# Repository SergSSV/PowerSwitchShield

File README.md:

Power Switch Shield with S202S02
================================

Simple shield with [2N7002](http://www.nxp.com/documents/data_sheet/2N7002.pdf) MOSFET to drive the [S202S02](http://www.sharpsma.com/webfm_send/303) Solid State Relay.  
The board is panelized to have two sub-boards with one S202S02 and also
a sub-board with three S202S02.

Boards are available from [dirtypcbs.com.](http://dirtypcbs.com/view.php?share=17641&accesskey=2531b32f0bd15d34d1d7f6f8c30357b9)

The PCB contains spare places to solder pull-up / pull-down resistors.  
Pull-Up: R5, R8, R12, R14, R16  
Pull-Down: R6, R7, R13, R15, R17

Resistors (R1, R3, R18, R19, R20) are calculated to get 20mA current at 3.3V supply.  
By using larger values (180R) it may also be used as a 5V shield.

#WARNING
**The shield is designed to switch main power.** So you must care about proper isolation.  
Don't use metal nuts or bolds to fix the board - only use plastic ones!  
For **inductive loads** (e.g. motors) either **connect a [snubber](https://www.google.de/?gws_rd=ssl#q=snubber+circuit)** (surge absorption) circuit as close as possible to the AC clamps or use a *S202S11*.

For AC current > 1A you should consider to use a heat sink (see datasheet "Fig.2 RMS ON-state Current vs. 
Ambient Temperature")!

[Sharp Documentation: Use of Solid State Relays (SSRs)](http://www.datasheetarchive.com/dlmain/SFDatasheet-3/sf-00061711.pdf)

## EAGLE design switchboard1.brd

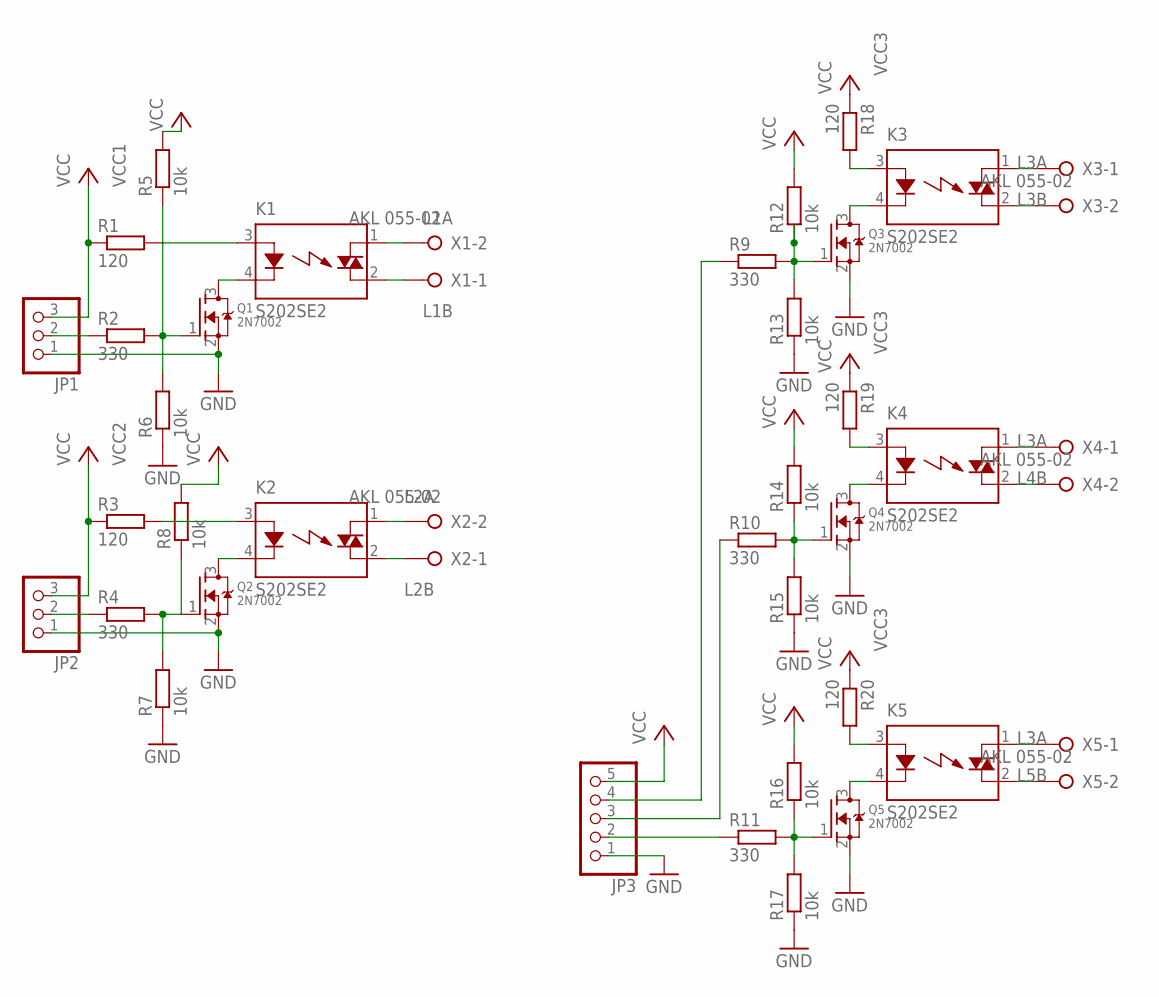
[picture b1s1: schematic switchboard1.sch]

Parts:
JP1, JP2: PINHD-1X3; 1X03
JP3: PINHD-1X5; 1X05
K1, K2, K3, K4, K5: S202SE2; S2XXEX
Q1, Q2, Q3, Q4, Q5: 2N7002; SOT23
R1, R3, R18, R19, R20: 120; R0805
R2, R4, R9, R10, R11: 330; R0805
R5, R6, R7, R8, R12, R13, R14, R15, R16, R17: 10k; R0805
X1, X2, X3, X4, X5: AKL 055-02; W237-132

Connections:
GND: JP1.1, JP2.1, JP3.1, Q1.2 (S), Q2.2 (S), Q3.2 (S), Q4.2 (S), Q5.2 (S), R6.1, R7.1, R13.1, R15.1, R17.1
L1A: K1.1 (DS1), X1.2
L1B: K1.2 (DS2), X1.1
L2A: K2.1 (DS1), X2.2
L2B: K2.2 (DS2), X2.1
L3A: K3.1 (DS1), K4.1 (DS1), K5.1 (DS1), X3.1, X4.1, X5.1
L3B: K3.2 (DS2), X3.2
L4B: K4.2 (DS2), X4.2
L5B: K5.2 (DS2), X5.2
unnamed: K1.4 (K), Q1.3 (D)
unnamed: K1.3 (A), R1.2
unnamed: Q1.1 (G), R2.2, R5.1, R6.2
unnamed: JP1.2, R2.1
unnamed: K2.3 (A), R3.2
unnamed: K2.4 (K), Q2.3 (D)
unnamed: Q2.1 (G), R4.2, R7.2, R8.1
unnamed: JP2.2, R4.1
unnamed: K3.3 (A), R18.2
unnamed: K3.4 (K), Q3.3 (D)
unnamed: Q3.1 (G), R9.2, R12.1, R13.2
unnamed: JP3.2, R11.1
unnamed: K4.3 (A), R19.2
unnamed: K4.4 (K), Q4.3 (D)
unnamed: Q4.1 (G), R10.2, R14.1, R15.2
unnamed: JP3.3, R10.1
unnamed: K5.3 (A), R20.2
unnamed: K5.4 (K), Q5.3 (D)
unnamed: Q5.1 (G), R11.2, R16.1, R17.2
unnamed: JP3.4, R9.1
VCC1: JP1.3, R1.1, R5.2
VCC2: JP2.3, R3.1, R8.2
VCC3: JP3.5, R12.2, R14.2, R16.2, R18.1, R19.1, R20.1

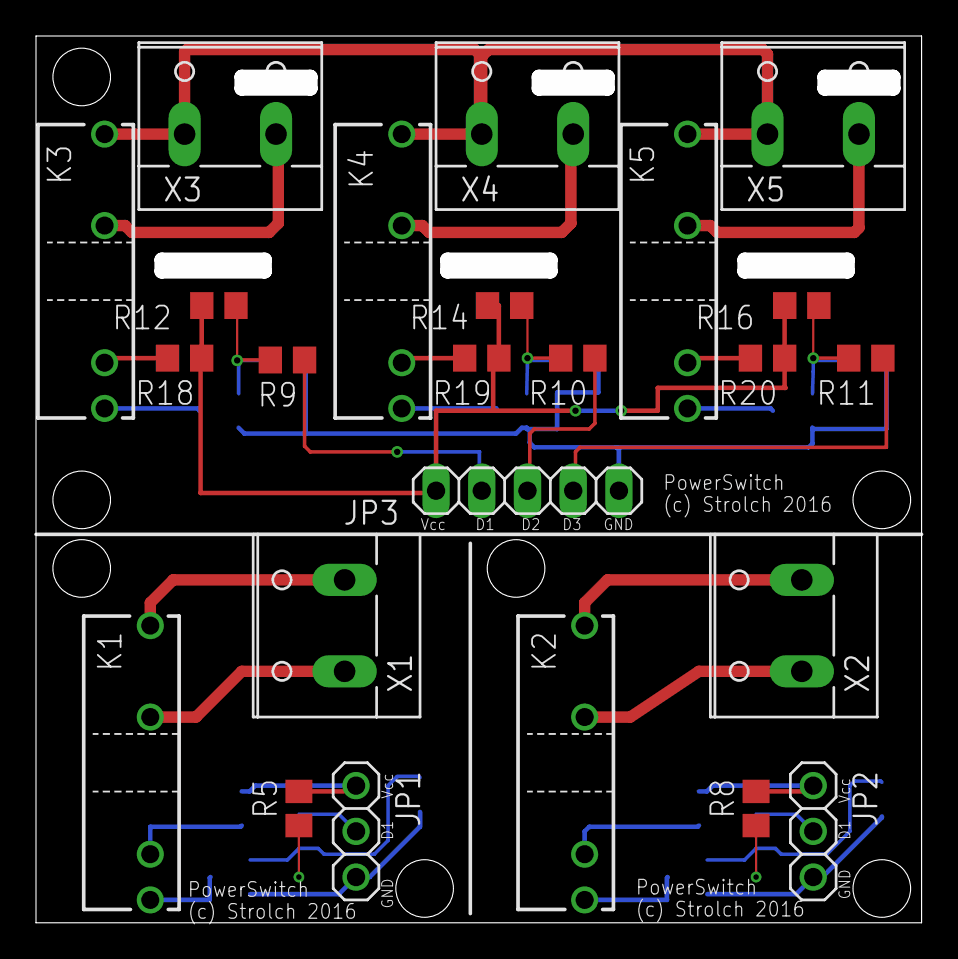
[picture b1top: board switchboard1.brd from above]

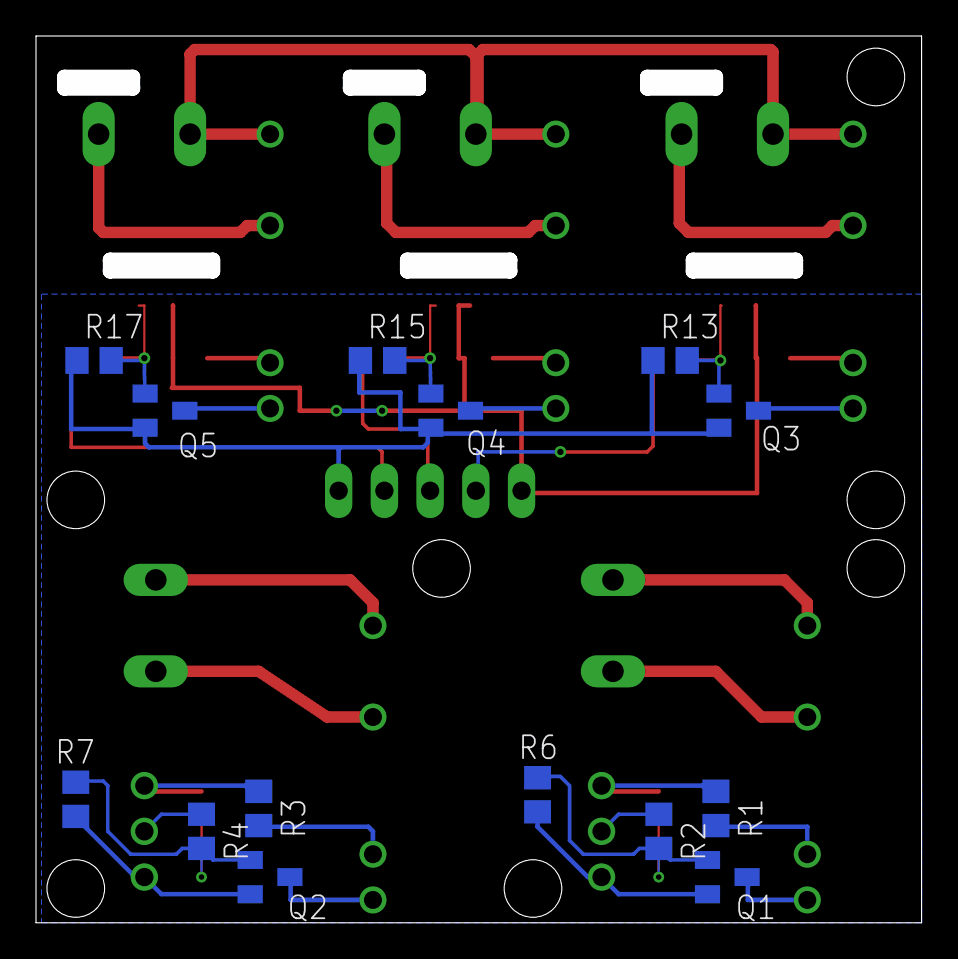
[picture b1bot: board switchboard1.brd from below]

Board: 2 copper layers, 48.4 x 48.5 mm, 38 parts (14 on the bottom side), 32 nets.

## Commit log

2016-03-03 Power Switch Shield with S202E02 SSR
2016-03-03 README: add linebreaks
2016-03-03 eye-candy
    add link to dirtypcbs.com
    add PCB top layer image
2016-03-03 README: add board image
2016-03-03 README.md: formatting...
2016-03-03 README.md: fix typo
2016-03-03 README.md: fix SSR product name
2016-03-03 README.md: add datasheet URLs for 2N7002, S202S02
2016-03-03 README.md: add WARNING section
2016-03-03 add snubber circuit schema
2016-03-03 add link to Sharp SSR documentation
2017-01-01 nothing special...
2017-01-01 Add Top/Bottom/Brd view
